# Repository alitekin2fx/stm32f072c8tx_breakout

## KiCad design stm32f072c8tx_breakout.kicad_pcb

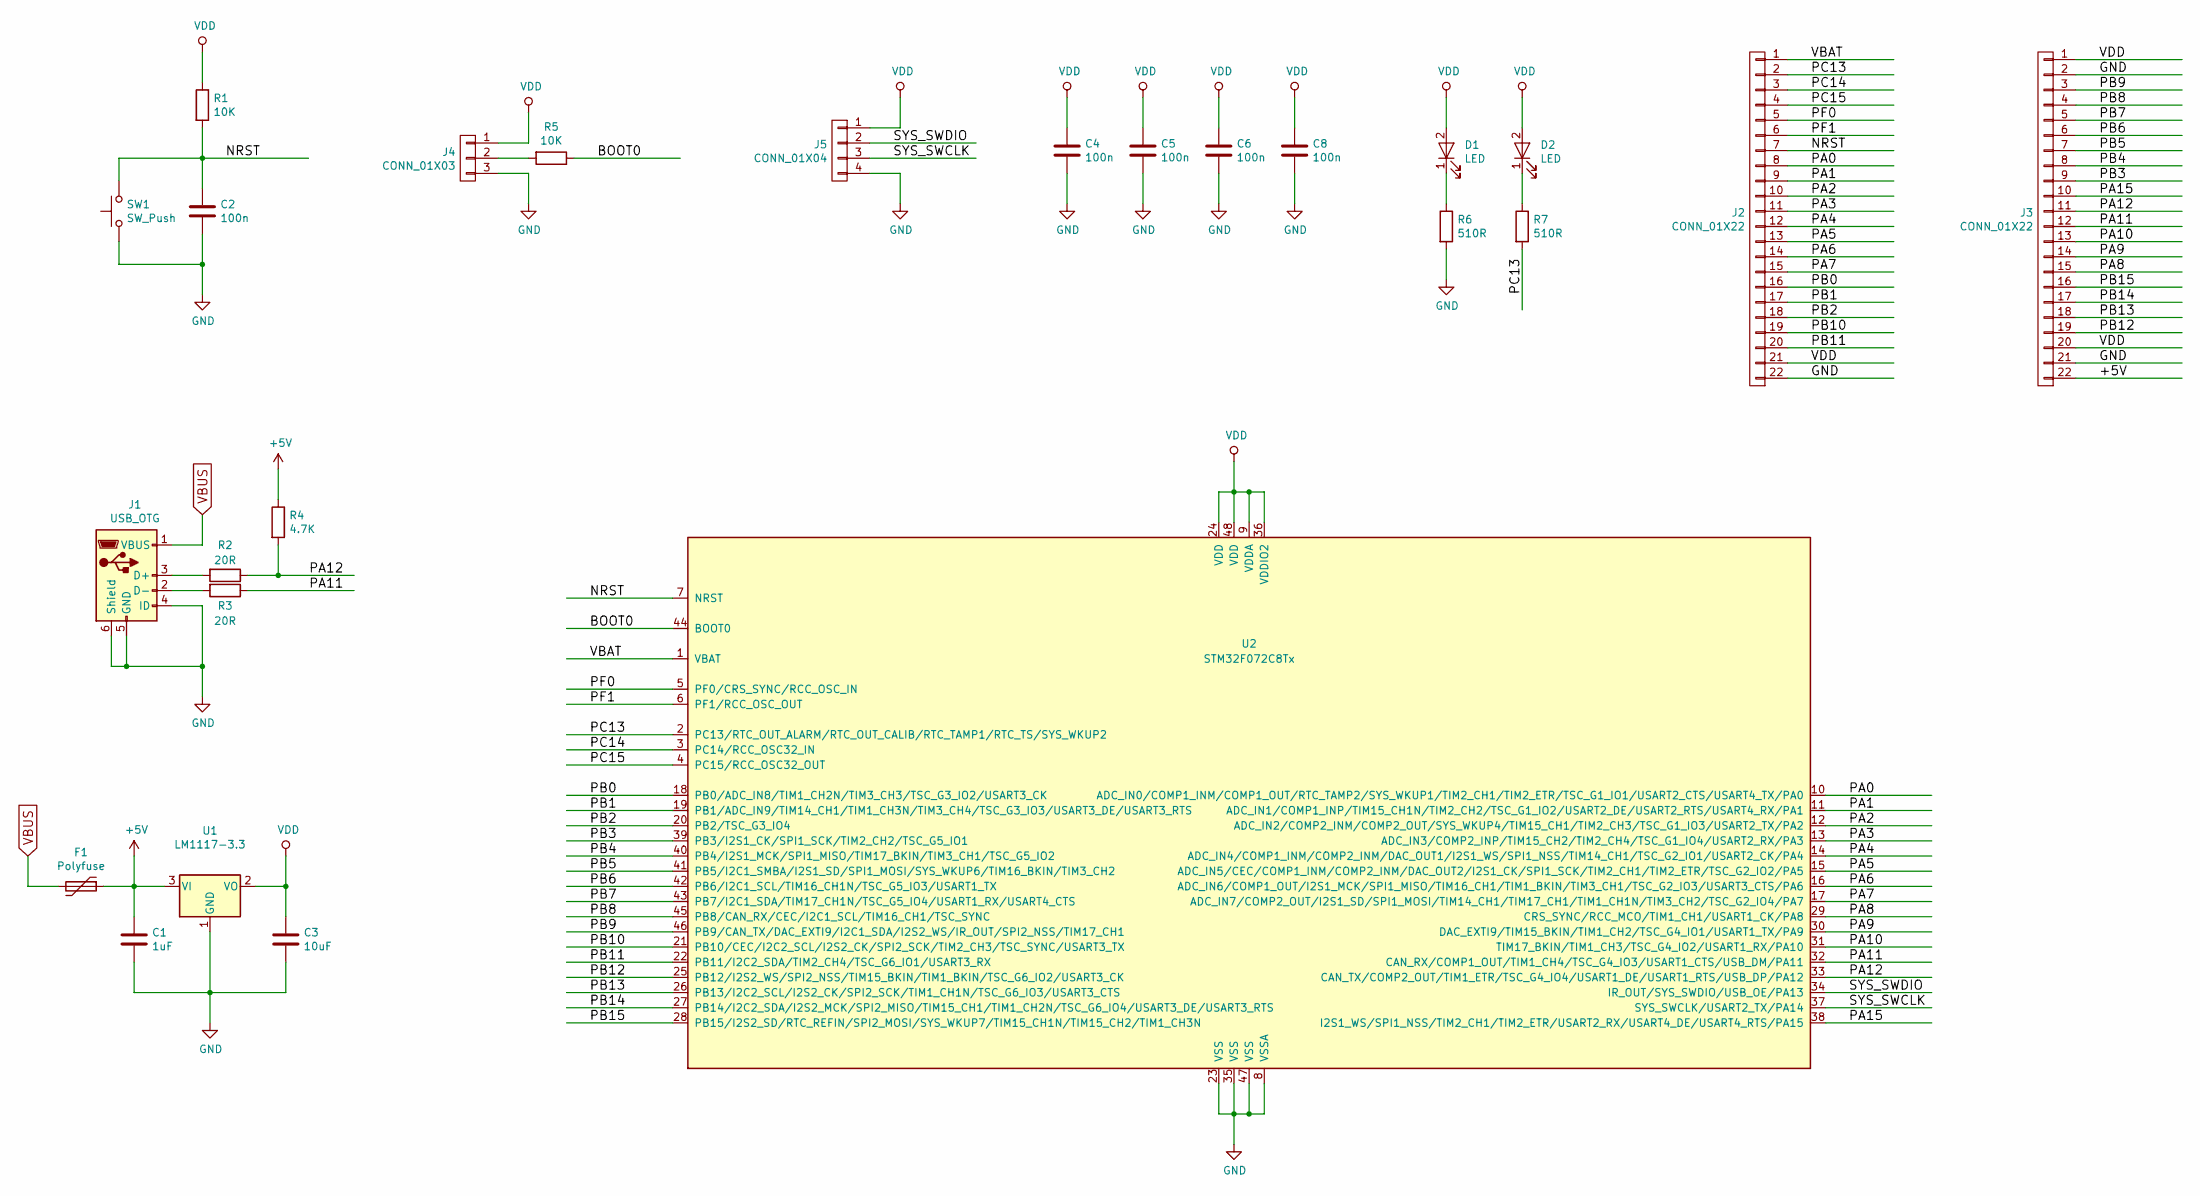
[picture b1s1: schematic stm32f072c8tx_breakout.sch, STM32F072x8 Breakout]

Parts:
C1: 1uF; C_1206
C2, C4, C5, C6, C8: 100n; C_0603
C3: 10uF; C_1206
D1, D2: LED; LED_0805
F1: Polyfuse; Fuse_SMD1206_Reflow
J1: USB_OTG; USB_Micro-B
J2, J3: CONN_01X22; Pin_Header_Straight_1x22_Pitch2.54mm
J4: CONN_01X03; Pin_Header_Straight_1x03_Pitch2.54mm
J5: CONN_01X04; Pin_Header_Straight_1x04_Pitch2.54mm
R1, R5: 10K; R_0603
R2, R3: 20R; R_0603
R4: 4.7K; R_0603
R6, R7: 510R; R_0603
SW1: SW_Push; SW_SPST_FSMSM
U1: LM1117-3.3; SOT-223-3Lead_TabPin2
U2: STM32F072C8Tx; LQFP-48_7x7mm_Pitch0.5mm

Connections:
+5V: C1.1, F1.1, J3.22, R4.1, U1.3 (VI)
/BOOT0: R5.1, U2.44 (BOOT0)
/NRST: C2.1, J2.7, R1.2, SW1.2, U2.7 (NRST)
/PA0: J2.8, U2.10 (ADC_IN0/COMP1_INM/COMP1_OUT/RTC_TAMP2/S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)
/PA1: J2.9, U2.11 (ADC_IN1/COMP1_INP/TIM15_CH1N/TIM2_CH2/T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)
/PA2: J2.10, U2.12 (ADC_IN2/COMP2_INM/COMP2_OUT/SYS_WKUP4/T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)
/PA3: J2.11, U2.13 (ADC_IN3/COMP2_INP/TIM15_CH2/TIM2_CH4/TS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)
/PA4: J2.12, U2.14 (ADC_IN4/COMP1_INM/COMP2_INM/DAC_OUT1/I2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)
/PA5: J2.13, U2.15 (ADC_IN5/CEC/COMP1_INM/COMP2_INM/DAC_OUT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)
/PA6: J2.14, U2.16 (ADC_IN6/COMP1_OUT/I2S1_MCK/SPI1_MISO/TI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)
/PA7: J2.15, U2.17 (ADC_IN7/COMP2_OUT/I2S1_SD/SPI1_MOSI/TIM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)
/PA8: J3.15, U2.29 (CRS_SYNC/RCC_MCO/TIM1_CH1/USART1_CK/PA8)
/PA9: J3.14, U2.30 (DAC_EXTI9/TIM15_BKIN/TIM1_CH2/TSC_G4_IO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)
/PA10: J3.13, U2.31 (TIM17_BKIN/TIM1_CH3/TSC_G4_IO2/USART1_R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)
/PA11: J3.12, R3.1, U2.32 (CAN_RX/COMP1_OUT/TIM1_CH4/TSC_G4_IO3/US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)
/PA12: J3.11, R2.1, R4.2, U2.33 (CAN_TX/COMP2_OUT/TIM1_ETR/TSC_G4_IO4/US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)
/PA15: J3.10, U2.38 (I2S1_WS/SPI1_NSS/TIM2_CH1/TIM2_ETR/USAR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)
/PB0: J2.16, U2.18 (PB0/ADC_IN8/TIM1_CH2N/TIM3_CH3/TSC_G3_I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)
/PB1: J2.17, U2.19 (PB1/ADC_IN9/TIM14_CH1/TIM1_CH3N/TIM3_CH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)
/PB2: J2.18, U2.20 (PB2/TSC_G3_IO4)
/PB3: J3.9, U2.39 (PB3/I2S1_CK/SPI1_SCK/TIM2_CH2/TSC_G5_IO1)
/PB4: J3.8, U2.40 (PB4/I2S1_MCK/SPI1_MISO/TIM17_BKIN/TIM3_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)
/PB5: J3.7, U2.41 (PB5/I2C1_SMBA/I2S1_SD/SPI1_MOSI/SYS_WKU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)
/PB6: J3.6, U2.42 (PB6/I2C1_SCL/TIM16_CH1N/TSC_G5_IO3/USAR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)
/PB7: J3.5, U2.43 (PB7/I2C1_SDA/TIM17_CH1N/TSC_G5_IO4/USAR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)
/PB8: J3.4, U2.45 (PB8/CAN_RX/CEC/I2C1_SCL/TIM16_CH1/TSC_S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)
/PB9: J3.3, U2.46 (PB9/CAN_TX/DAC_EXTI9/I2C1_SDA/I2S2_WS/I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)
/PB10: J2.19, U2.21 (PB10/CEC/I2C2_SCL/I2S2_CK/SPI2_SCK/TIM2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)
/PB11: J2.20, U2.22 (PB11/I2C2_SDA/TIM2_CH4/TSC_G6_IO1/USART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)
/PB12: J3.19, U2.25 (PB12/I2S2_WS/SPI2_NSS/TIM15_BKIN/TIM1_B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)
/PB13: J3.18, U2.26 (PB13/I2C2_SCL/I2S2_CK/SPI2_SCK/TIM1_CH1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)
/PB14: J3.17, U2.27 (PB14/I2C2_SDA/I2S2_MCK/SPI2_MISO/TIM15_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)
/PB15: J3.16, U2.28 (PB15/I2S2_SD/RTC_REFIN/SPI2_MOSI/SYS_WK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)
/PC13: J2.2, R7.2, U2.2 (PC13/RTC_OUT_ALARM/RTC_OUT_CALIB/RTC_TA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)
/PC14: J2.3, U2.3 (PC14/RCC_OSC32_IN)
/PC15: J2.4, U2.4 (PC15/RCC_OSC32_OUT)
/PF0: J2.5, U2.5 (PF0/CRS_SYNC/RCC_OSC_IN)
/PF1: J2.6, U2.6 (PF1/RCC_OSC_OUT)
/SYS_SWCLK: J5.3, U2.37 (SYS_SWCLK/USART2_TX/PA14)
/SYS_SWDIO: J5.2, U2.34 (IR_OUT/SYS_SWDIO/USB_OE/PA13)
/VBAT: J2.1, U2.1 (VBAT)
GND: C1.2, C2.2, C3.2, C4.2, C5.2, C6.2, C8.2, J1.4 (ID), J1.5 (GND), J1.6 (Shield), J2.22, J3.2, J3.21, J4.3, J5.4, R6.2, SW1.1, U1.1 (GND), U2.8 (VSSA), U2.23 (VSS), U2.35 (VSS), U2.47 (VSS)
unnamed: D1.1 (K), R6.1
unnamed: D2.1 (K), R7.1
unnamed: J1.2 (D-), R3.2
unnamed: J1.3 (D+), R2.2
unnamed: J4.2, R5.2
VBUS: F1.2, J1.1 (VBUS)
VDD: C3.1, C4.1, C5.1, C6.1, C8.1, D1.2 (A), D2.2 (A), J2.21, J3.1, J3.20, J4.1, J5.1, R1.1, U1.2 (VO), U2.9 (VDDA), U2.24 (VDD), U2.36 (VDDIO2), U2.48 (VDD)

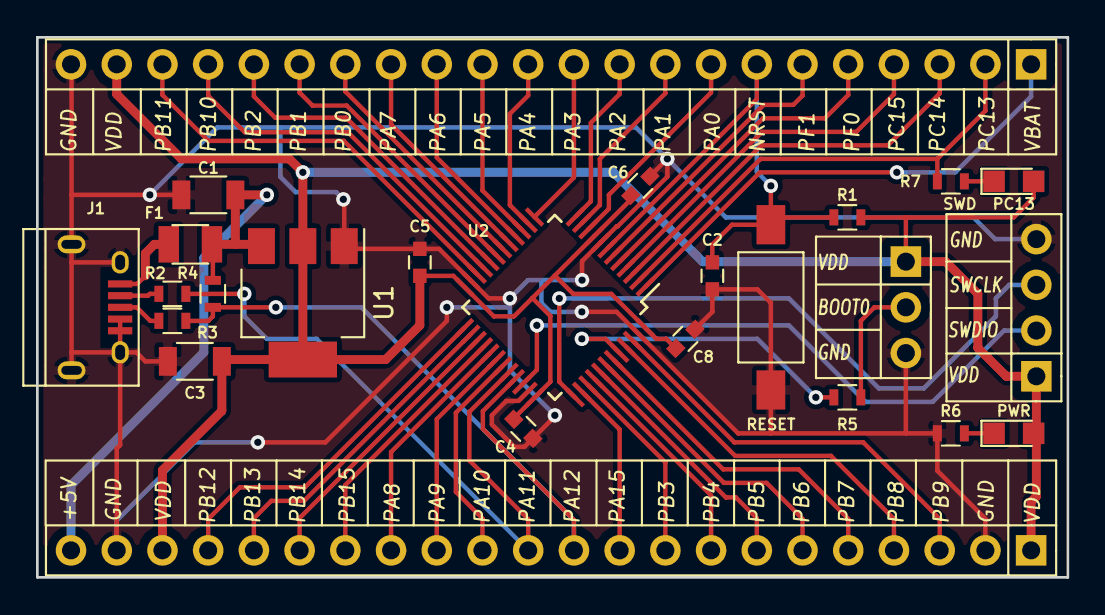
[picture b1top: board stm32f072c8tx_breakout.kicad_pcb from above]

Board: 2 copper layers, 57.2 x 30.0 mm, 25 parts (0 on the bottom side), 49 nets.

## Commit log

2017-07-04 PCB changes
